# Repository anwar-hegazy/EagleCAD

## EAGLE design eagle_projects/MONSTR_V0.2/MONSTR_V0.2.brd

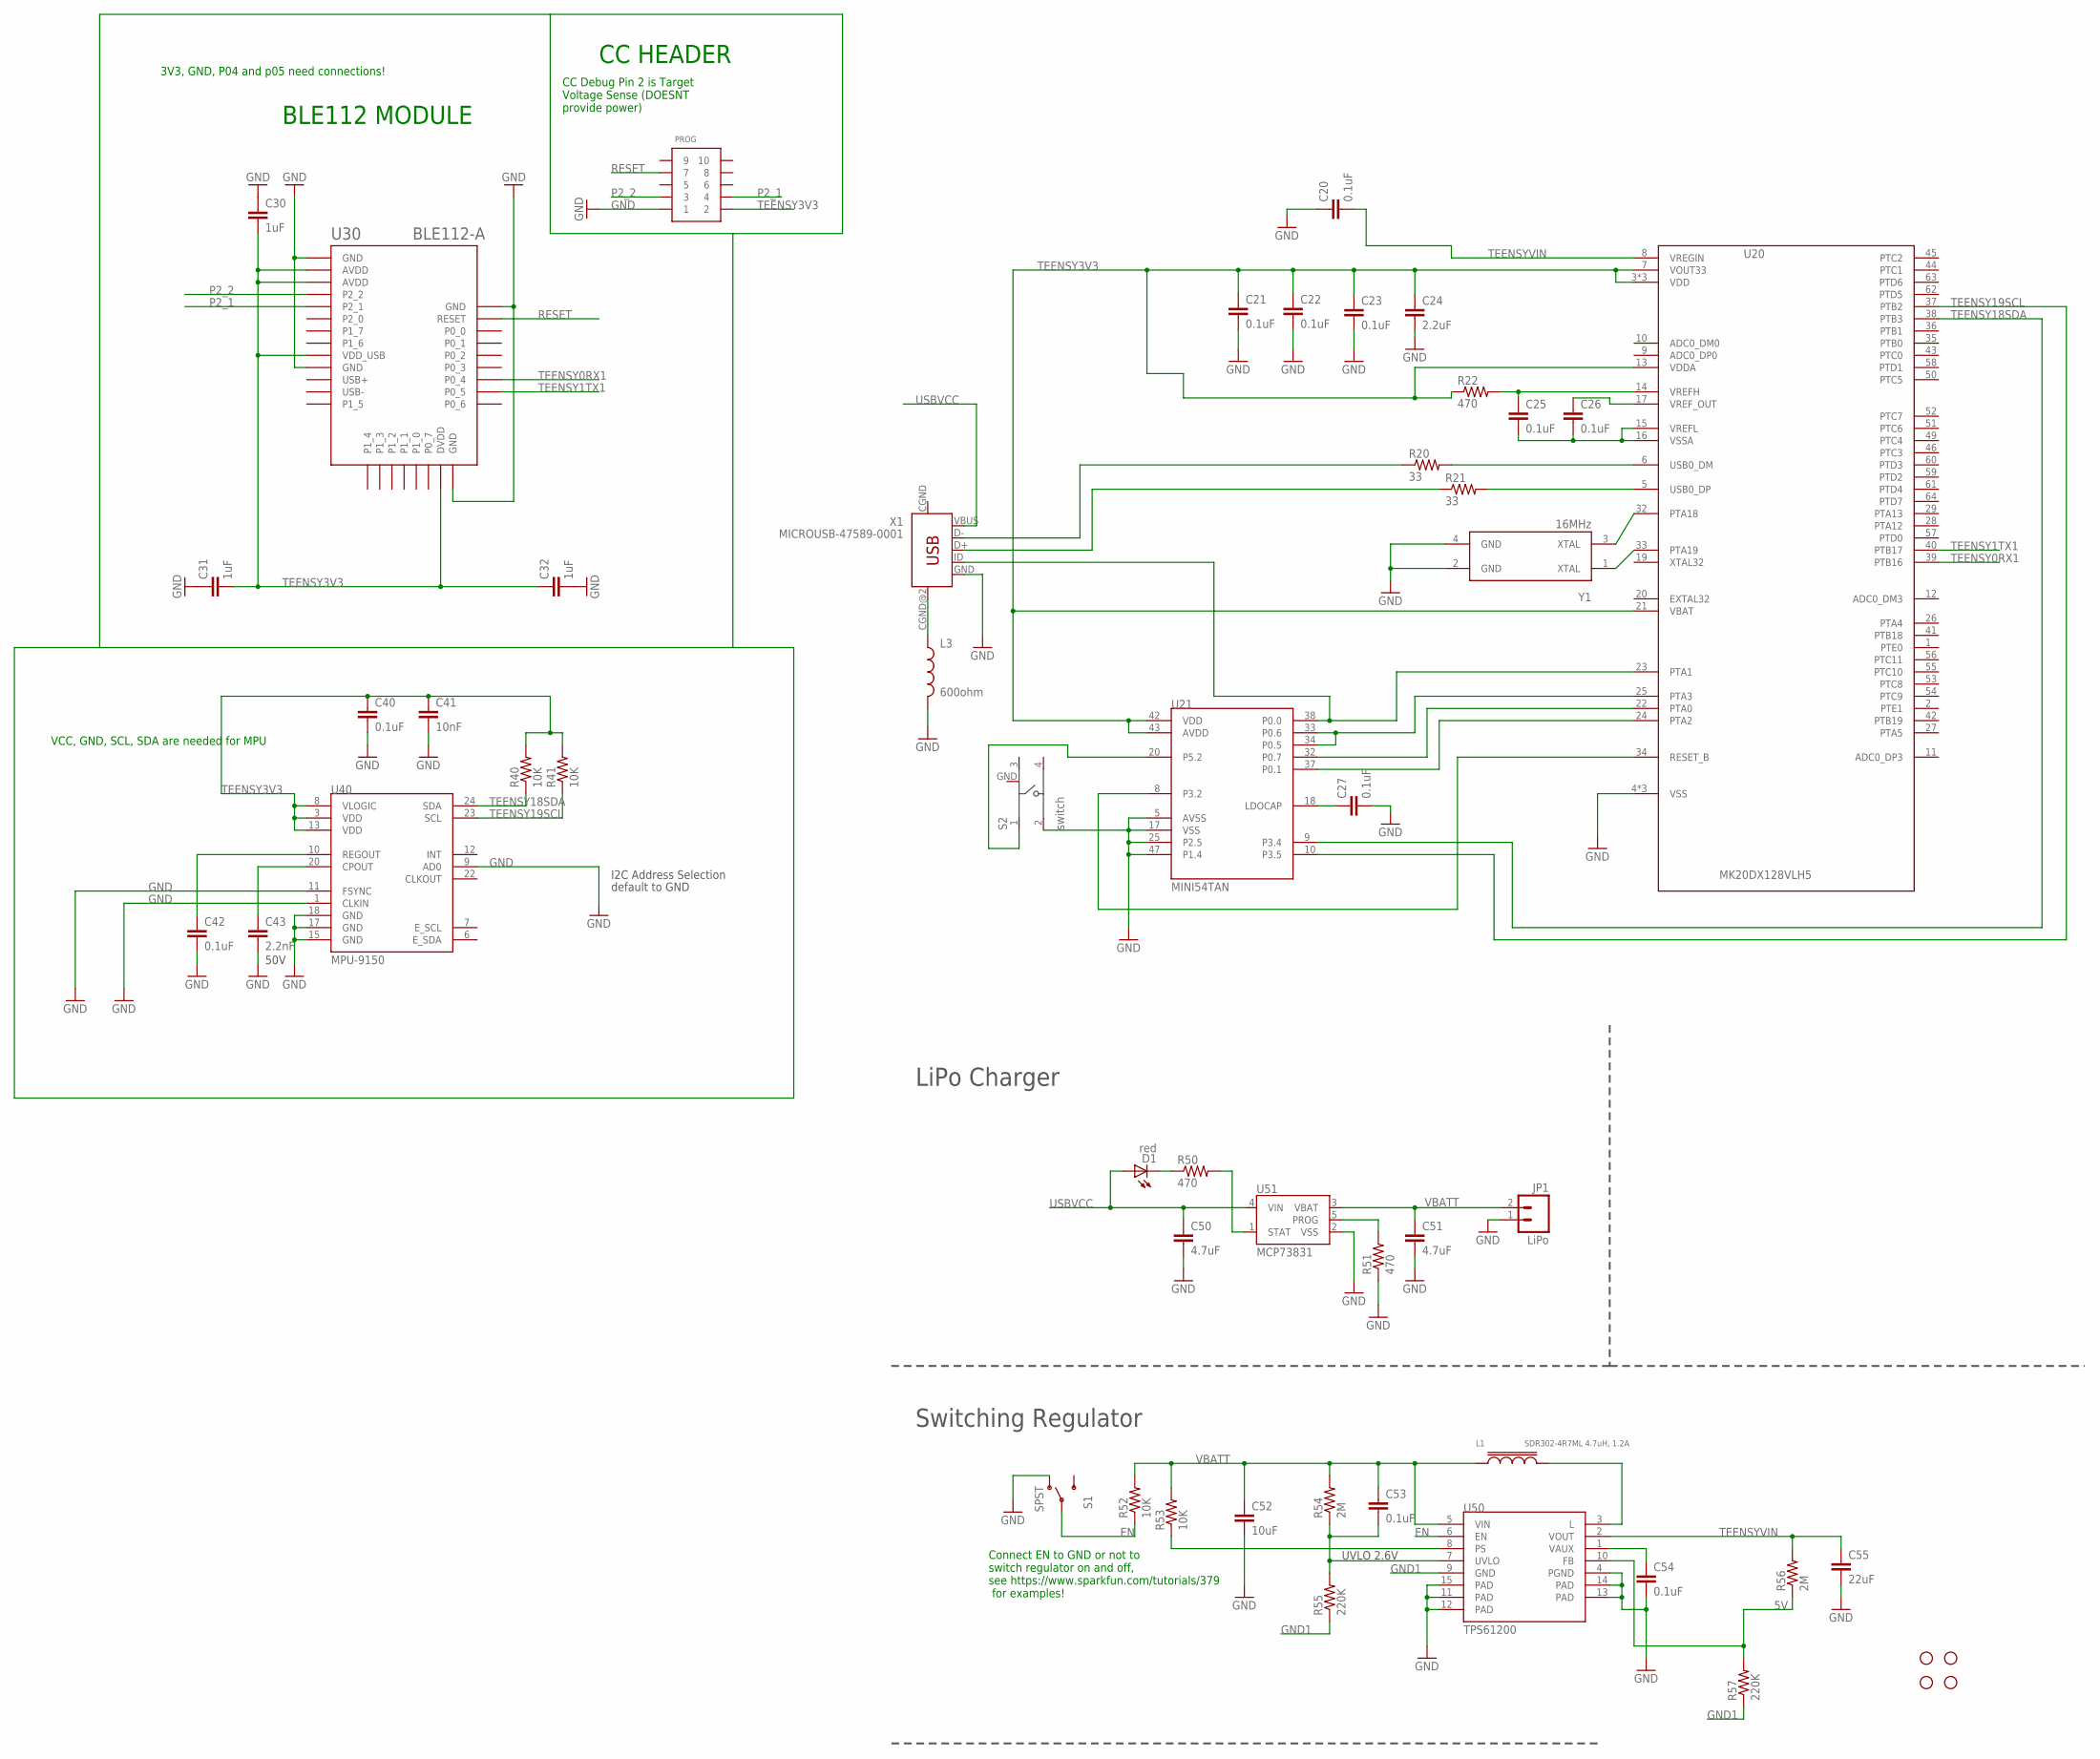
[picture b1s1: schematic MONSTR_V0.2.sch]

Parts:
C20, C21, C22, C23, C25, C26, C27, C40, C42, C53, C54: 0.1uF; 0402-CAP
C24: 2.2uF; 0402-CAP
C30, C31, C32: 1uF; 0402-CAP
C41: 10nF; 0402-CAP
C43: 2.2nF; 0402-CAP
C50, C51: 4.7uF; 0402-CAP
C52: 10uF; 0402-CAP
C55: 22uF; 0603-CAP
D1: red; LED-0603
JP1: LiPo; JST-2-SMD
JP7, JP8, JP9, JP10: STAND-OFF
L1: SDR302-4R7ML 4.7uH, 1.2A; BOURNS-SDR0302-SERIES-INDUCTOR
L3: 600ohm; 0805
PROG: CONN_5-2-FTSH-V; FTSH-105-DV
R20, R21: 33; 0402-RES
R22, R50, R51: 470; 0402-RES
R40, R41, R52, R53: 10K; 0402-RES
R54, R56: 2M; 0402-RES
R55, R57: 220K; 0402-RES
S1: SPST; SWITCH-SPST-SMD-A
S2: switch; 101-IG
U20: MK20DX128VLH5
U21: MINI54TAN
U30: BLE112-A
U40: MPU-9150; QFN-24-NP
U50: TPS61200; QFN-10_PAD
U51: MCP73831; SOT23-5
X1: MICROUSB-47589-0001
Y1: 16MHz; CRYSTAL-SMD-3.2_2.5MM

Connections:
5V: R56.1, R57.2, U50.10 (FB)
EN: R52.1, S1.2, U50.6 (EN)
GND: C20.1, C21.2, C22.2, C23.2, C24.2, C27.2, C30.1, C31.1, C32.2, C40.2, C41.2, C42.2, C43.2, C50.2, C51.2, C52.2, C54.2, C55.2, JP1.1, L3.2, PROG.1, R51.1, S1.1 (O), S2.2, S2.GND, U20.4 (VSS), U20.31 (VSS), U20.47 (VSS), U21.5 (AVSS), U21.17 (VSS), U21.25 (P2.5), U21.47 (P1.4), U30.GND1 (GND), U30.GND2 (GND), U30.GND3 (GND), U30.GND4 (GND), U40.1 (CLKIN), U40.9 (AD0), U40.11 (FSYNC), U40.15 (GND), U40.17 (GND), U40.18 (GND), U50.4 (PGND), U50.11 (PAD), U50.12 (PAD), U50.13 (PAD), U50.14 (PAD), U50.15 (PAD), U51.2 (VSS), X1.GND, Y1.2 (GND), Y1.4 (GND)
GND1: R55.1, R57.1, U50.9 (GND)
unnamed: C43.1, U40.20 (CPOUT)
unnamed: C42.1, U40.10 (REGOUT)
unnamed: R53.1, U50.8 (PS)
unnamed: R51.2, U51.5 (PROG)
unnamed: R50.2, U51.1 (STAT)
unnamed: U20.32 (PTA18), Y1.3 (XTAL)
unnamed: U20.33 (PTA19), Y1.1 (XTAL)
unnamed: C25.2, C26.2, U20.15 (VREFL), U20.16 (VSSA)
unnamed: R20.2, U20.6 (USB0_DM)
unnamed: R21.2, U20.5 (USB0_DP)
unnamed: R20.1, X1.D-
unnamed: R21.1, X1.D+
unnamed: L3.1, X1.CGND@2 (MTN4)
unnamed: C26.1, U20.17 (VREF_OUT)
unnamed: C25.1, R22.2, U20.14 (VREFH)
unnamed: U20.23 (PTA1), U21.38 (P0.0), X1.ID
unnamed: U20.25 (PTA3), U21.33 (P0.6), U21.34 (P0.5)
unnamed: U20.22 (PTA0), U21.32 (P0.7)
unnamed: U20.24 (PTA2), U21.37 (P0.1)
unnamed: S2.1, U21.20 (P5.2)
unnamed: U20.34 (RESET_B), U21.8 (P3.2)
unnamed: C27.1, U21.18 (LDOCAP)
unnamed: D1.C, R50.1
unnamed: L1.2, U50.3 (L)
unnamed: C54.1, U50.1 (VAUX)
P2_1: PROG.4, U30.P2_1
P2_2: PROG.3, U30.P2_2
RESET: PROG.7, U30.RESET
TEENSY0RX1: U20.39 (PTB16), U30.P0_4
TEENSY1TX1: U20.40 (PTB17), U30.P0_5
TEENSY3V3: C21.1, C22.1, C23.1, C24.1, C30.2, C31.2, C32.1, C40.1, C41.1, PROG.2, R22.1, R40.2, R41.2, U20.3 (VDD), U20.7 (VOUT33), U20.13 (VDDA), U20.21 (VBAT), U20.30 (VDD), U20.48 (VDD), U21.42 (VDD), U21.43 (AVDD), U30.AVDD1 (AVDD), U30.AVDD2 (AVDD), U30.DVDD, U30.VDD_USB, U40.3 (VDD), U40.8 (VLOGIC), U40.13 (VDD)
TEENSY18SDA: R40.1, U20.38 (PTB3), U21.9 (P3.4), U40.24 (SDA)
TEENSY19SCL: R41.1, U20.37 (PTB2), U21.10 (P3.5), U40.23 (SCL)
TEENSYVIN: C20.2, C55.1, R56.2, U20.8 (VREGIN), U50.2 (VOUT)
USBVCC: C50.1, D1.A, U51.4 (VIN), X1.VBUS
UVLO: C53.2, R54.1, R55.2, U50.7 (UVLO)
VBATT: C51.1, C52.1, C53.1, JP1.2, L1.1, R52.2, R53.2, R54.2, U50.5 (VIN), U51.3 (VBAT)

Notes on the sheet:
50V
I2C Address Selection
default to GND
CC HEADER
BLE112 MODULE
VCC, GND, SCL, SDA are needed for MPU
UVLO 2.6V
LiPo Charger
Switching Regulator
Connect EN to GND or not to switch regulator on and off, see https://www.sparkfun.com/tutorials/379 for examples!
3V3, GND, P04 and p05 need connections!
CC Debug Pin 2 is Target Voltage Sense (DOESNT provide power)

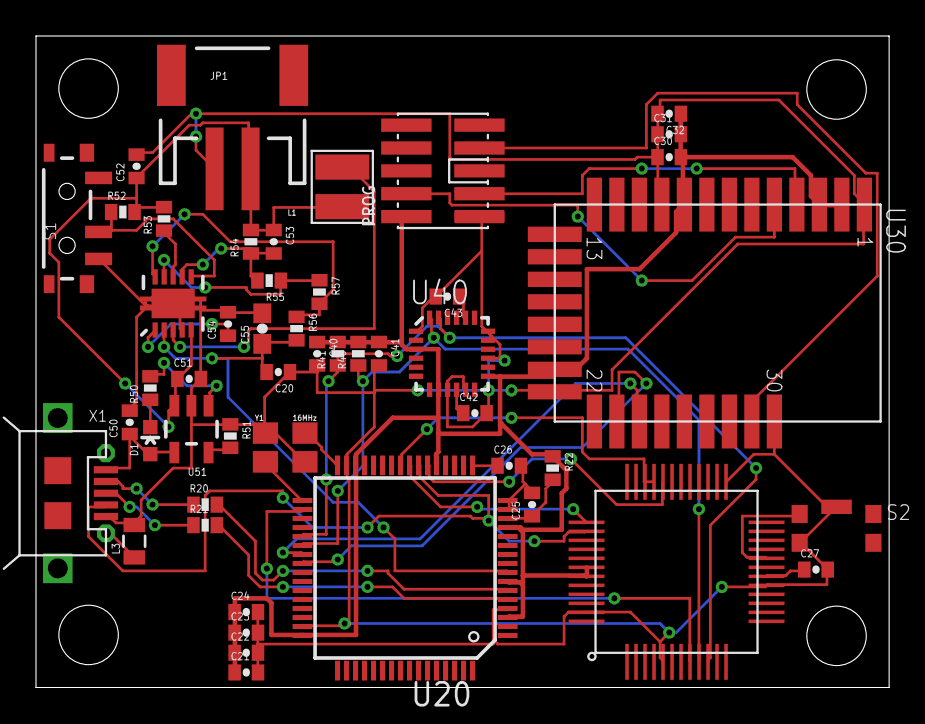
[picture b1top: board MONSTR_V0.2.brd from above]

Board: 2 copper layers, 47.4 x 36.2 mm, 53 parts (0 on the bottom side), 41 nets.

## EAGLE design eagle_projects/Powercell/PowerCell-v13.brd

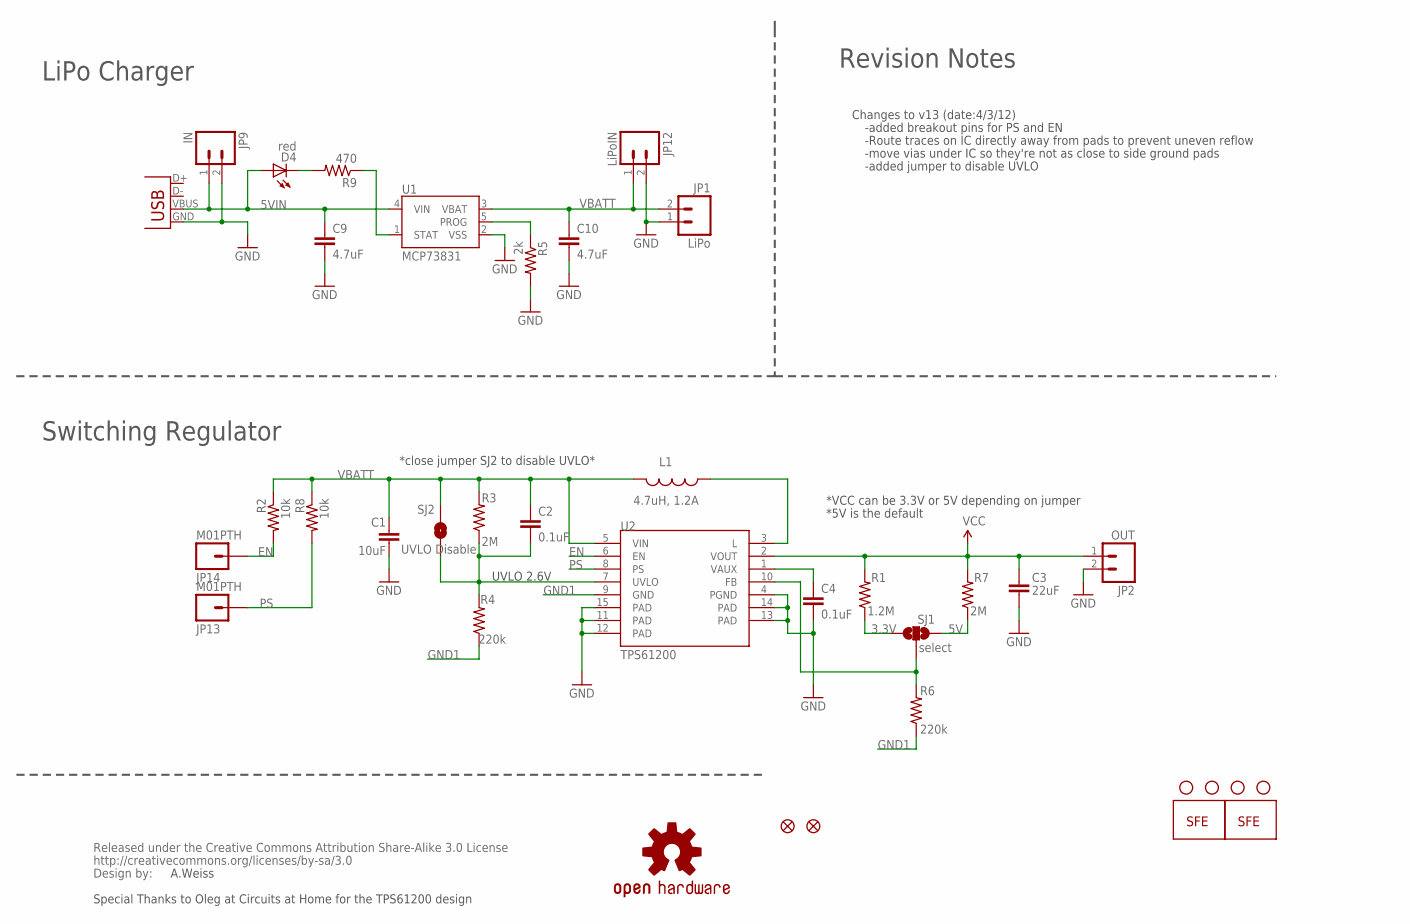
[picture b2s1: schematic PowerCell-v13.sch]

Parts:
C1: 10uF; 1206
C2, C4: 0.1uF; 0402-CAP
C3: 22uF; 0805
C9, C10: 4.7uF; 0402-CAP
D4: red; LED-0603
JP1: LiPo; JST-2-SMD
JP2: OUT; 1X02
JP3: LOGO-SFENEW; SFE-NEW-WEBLOGO
JP4: LOGO-SFESK; SFE-LOGO-FLAME
JP5, JP6, JP7, JP8: STAND-OFF
JP9: IN; 1X02
JP12: LiPoIN; 1X02
JP13, JP14: M01PTH; 1X01
JP15, JP16: FIDUCIALUFIDUCIAL; MICRO-FIDUCIAL
L1: 4.7uH, 1.2A; CDRH2D09
R1: 1.2M; 0402-RES
R2, R8: 10k; 0402-RES
R3, R7: 2M; 0402-RES
R4, R6: 220k; 0402-RES
R5: 2k; 0402-RES
R9: 470; 0402-RES
SJ1: select; SJ_3_PASTE2&3
SJ2: UVLO Disable; SJ_2S-NO
U1: MCP73831; SOT23-5
U2: TPS61200; QFN-10_PAD
U$1: OSHW-LOGOS; OSHW-LOGO-S
U$2: CREATIVE_COMMONS
X1: USB-MICROB

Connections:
3.3V: R1.1, SJ1.1
5V: R7.1, SJ1.3
5VIN: C9.1, D4.A, JP9.1, U1.4 (VIN), X1.VBUS
EN: JP14.1, R2.2, U2.6 (EN)
FB: R6.2, SJ1.2, U2.10 (FB)
GND: C1.2, C3.2, C4.2, C9.2, C10.2, JP1.1, JP2.2, JP9.2, JP12.2, R5.2, U1.2 (VSS), U2.4 (PGND), U2.11 (PAD), U2.12 (PAD), U2.13 (PAD), U2.14 (PAD), U2.15 (PAD), X1.GND
GND1: R4.1, R6.1, U2.9 (GND)
unnamed: C4.1, U2.1 (VAUX)
unnamed: L1.P$1 (1), U2.3 (L)
unnamed: D4.C, R9.2
unnamed: R5.1, U1.5 (PROG)
unnamed: R9.1, U1.1 (STAT)
PS: JP13.1, R8.2, U2.8 (PS)
UVLO: C2.2, R3.1, R4.2, SJ2.1, U2.7 (UVLO)
VBATT: C1.1, C2.1, C10.1, JP1.2, JP12.1, L1.P$2 (2), R2.1, R3.2, R8.1, SJ2.2, U1.3 (VBAT), U2.5 (VIN)
VCC: C3.1, JP2.1, R1.2, R7.2, U2.2 (VOUT)

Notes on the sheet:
UVLO 2.6V
Changes to v13 (date:4/3/12)
-added breakout pins for PS and EN
-Route traces on IC directly away from pads to prevent uneven reflow
-move vias under IC so they're not as close to side ground pads
*close jumper SJ2 to disable UVLO*
-added jumper to disable UVLO
A.Weiss
Special Thanks to Oleg at Circuits at Home for the TPS61200 design
LiPo Charger
Switching Regulator
Revision Notes
*VCC can be 3.3V or 5V depending on jumper
*5V is the default

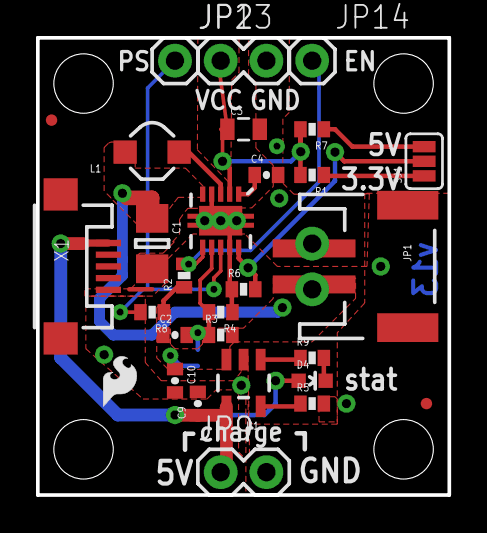
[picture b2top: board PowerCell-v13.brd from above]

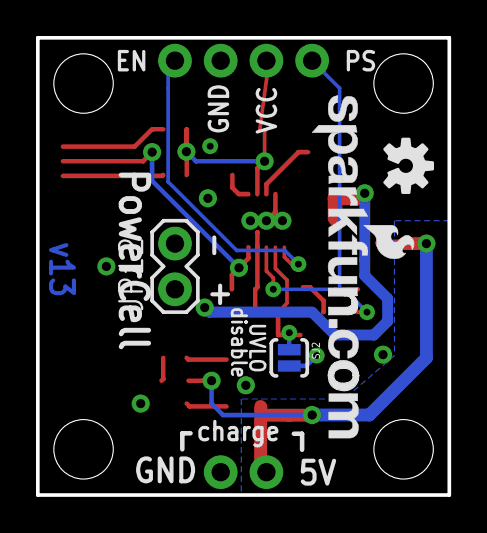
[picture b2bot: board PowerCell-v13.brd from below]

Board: 2 copper layers, 22.9 x 25.4 mm, 38 parts (4 on the bottom side), 16 nets.

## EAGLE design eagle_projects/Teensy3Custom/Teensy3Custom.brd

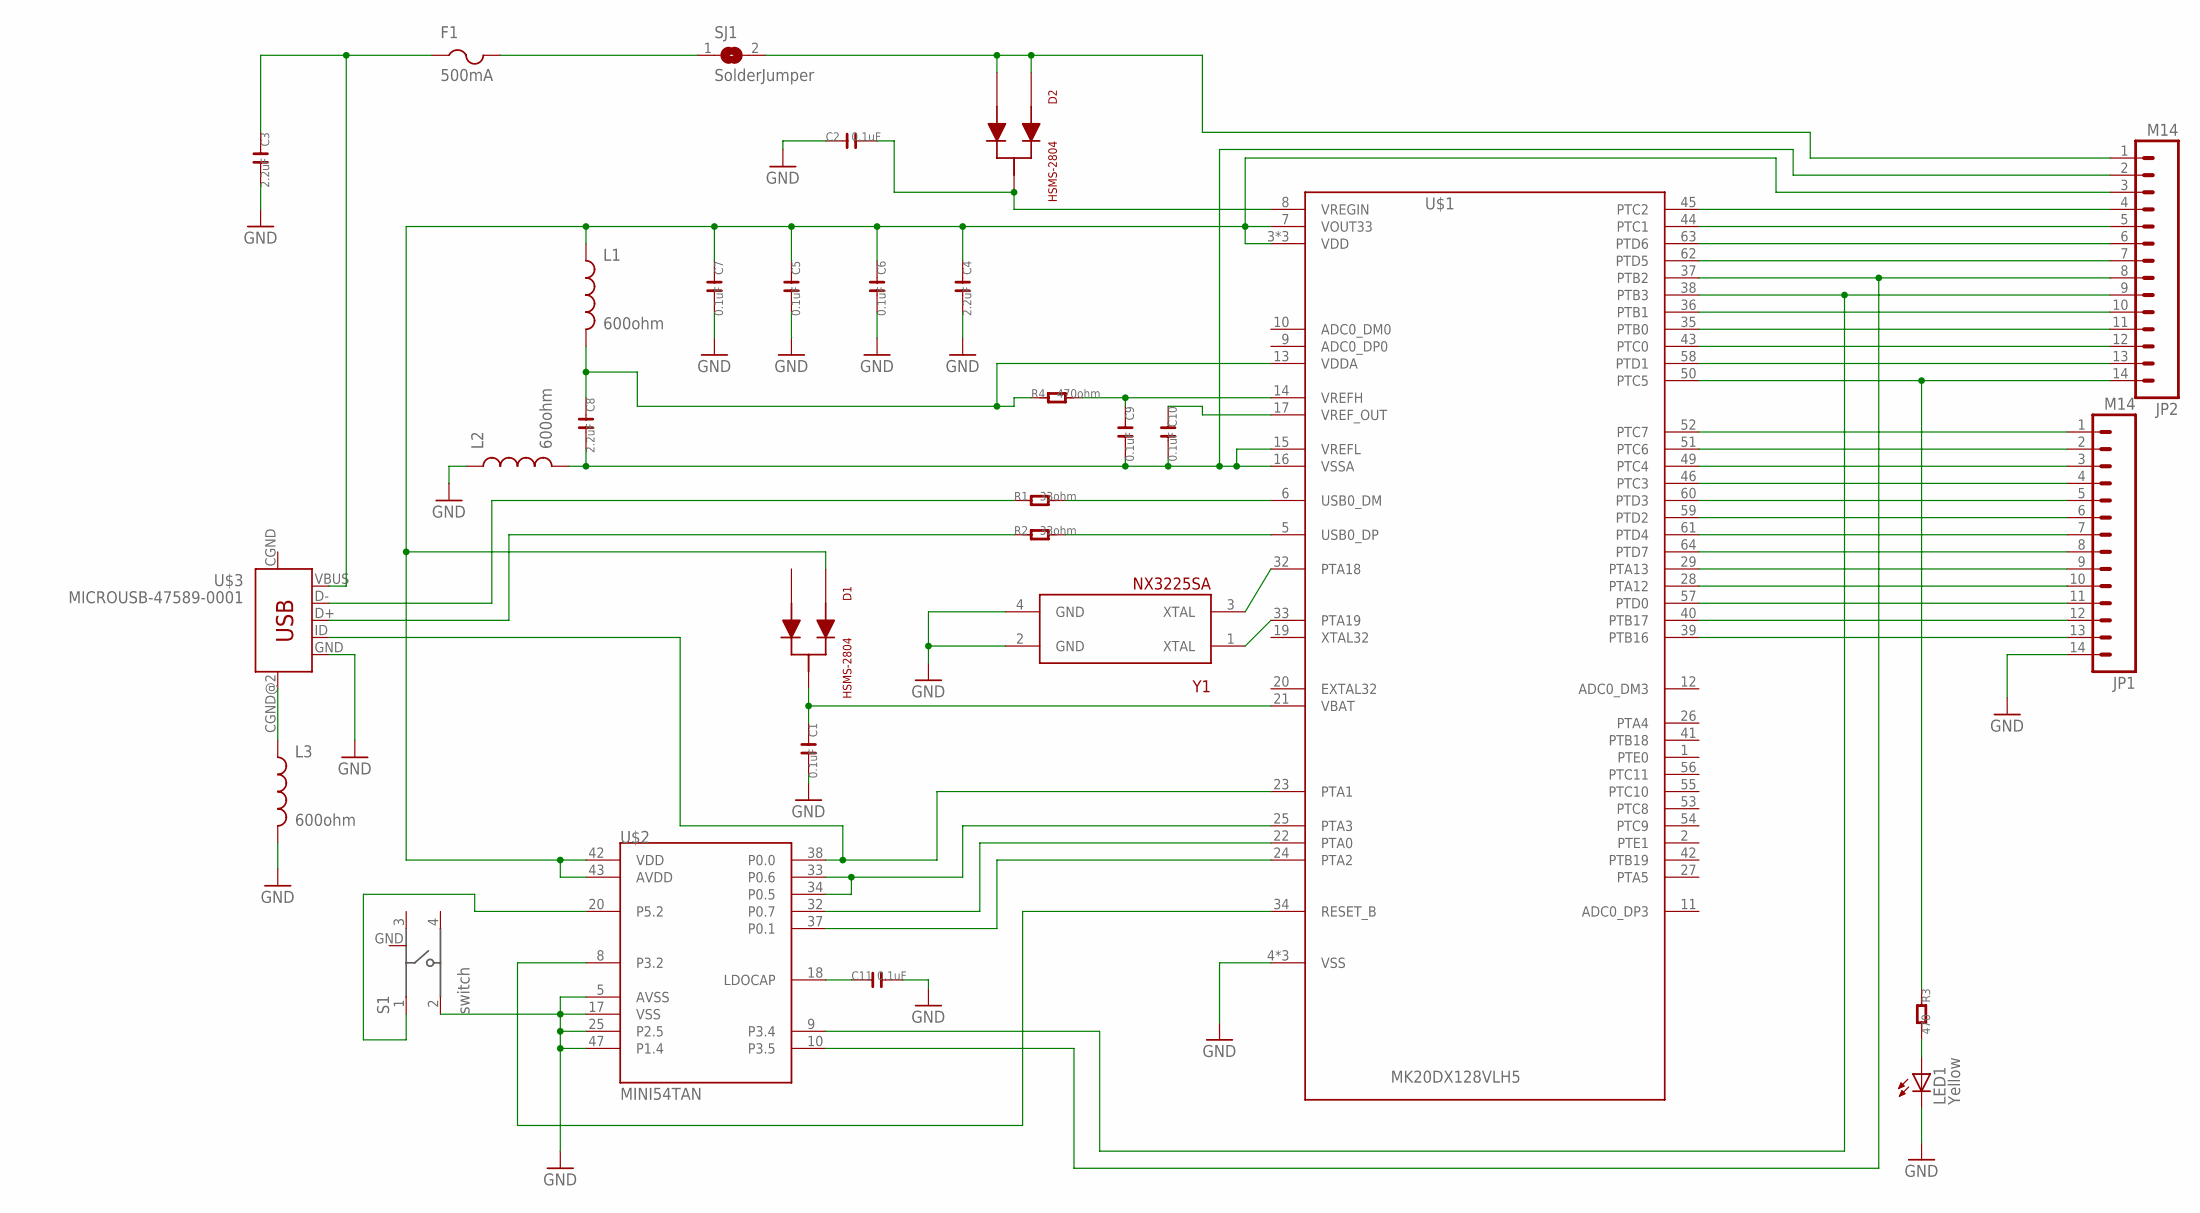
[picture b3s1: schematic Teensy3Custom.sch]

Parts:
C1, C2, C5, C6, C7, C9, C10, C11: 0.1uF; C0603
C3, C4, C8: 2.2uF; C0603
D1, D2: HSMS-2804; SOT-23-DIODE
F1: 500mA; R1206
JP1, JP2: M14; 1X14
L1, L2, L3: 600ohm; 0805
LED1: Yellow; CHIP-LED0603
R1, R2: 33ohm; R0603
R3: 470; R0603
R4: 470ohm; R0603
S1: switch; 101-IG
SJ1: SolderJumper; SJ
U$1: MK20DX128VLH5
U$2: MINI54TAN
U$3: MICROUSB-47589-0001
Y1: NX3225SA; CRYSTAL-SMD-3.2_2.5MM

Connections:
GND: C1.2, C2.1, C3.2, C4.2, C5.2, C6.2, C7.2, C11.2, JP1.14, L2.1, L3.2, LED1.C, S1.2, S1.GND, U$1.4 (VSS), U$1.31 (VSS), U$1.47 (VSS), U$2.5 (AVSS), U$2.17 (VSS), U$2.25 (P2.5), U$2.47 (P1.4), U$3.GND, Y1.2 (GND), Y1.4 (GND)
unnamed: U$1.32 (PTA18), Y1.3 (XTAL)
unnamed: U$1.33 (PTA19), Y1.1 (XTAL)
unnamed: C1.1, D1.3 (OUT), U$1.21 (VBAT)
unnamed: D2.1 (IN), D2.2 (IN), JP2.1, SJ1.2
unnamed: F1.2, SJ1.1
unnamed: C3.1, F1.1, U$3.VBUS
unnamed: C2.2, D2.3 (OUT), U$1.8 (VREGIN)
unnamed: C4.1, C5.1, C6.1, C7.1, D1.1 (IN), JP2.3, L1.1, U$1.3 (VDD), U$1.7 (VOUT33), U$1.30 (VDD), U$1.48 (VDD), U$2.42 (VDD), U$2.43 (AVDD)
unnamed: C8.2, C9.2, C10.2, JP2.2, L2.2, U$1.15 (VREFL), U$1.16 (VSSA)
unnamed: C8.1, L1.2, R4.1, U$1.13 (VDDA)
unnamed: R2.2, U$1.5 (USB0_DP)
unnamed: R1.1, U$3.D-
unnamed: R1.2, U$1.6 (USB0_DM)
unnamed: R2.1, U$3.D+
unnamed: L3.1, U$3.CGND@2 (MTN4)
unnamed: U$1.25 (PTA3), U$2.33 (P0.6), U$2.34 (P0.5)
unnamed: C10.1, U$1.17 (VREF_OUT)
unnamed: C9.1, R4.2, U$1.14 (VREFH)
unnamed: LED1.A, R3.2
unnamed: JP2.14, R3.1, U$1.50 (PTC5)
unnamed: S1.1, U$2.20 (P5.2)
unnamed: U$1.23 (PTA1), U$2.38 (P0.0), U$3.ID
unnamed: U$1.22 (PTA0), U$2.32 (P0.7)
unnamed: U$1.24 (PTA2), U$2.37 (P0.1)
unnamed: JP2.9, U$1.38 (PTB3), U$2.9 (P3.4)
unnamed: JP2.8, U$1.37 (PTB2), U$2.10 (P3.5)
unnamed: U$1.34 (RESET_B), U$2.8 (P3.2)
unnamed: JP2.4, U$1.45 (PTC2)
unnamed: JP2.5, U$1.44 (PTC1)
unnamed: JP2.6, U$1.63 (PTD6)
unnamed: JP2.7, U$1.62 (PTD5)
unnamed: JP2.10, U$1.36 (PTB1)
unnamed: JP2.11, U$1.35 (PTB0)
unnamed: JP2.12, U$1.43 (PTC0)
unnamed: JP2.13, U$1.58 (PTD1)
unnamed: JP1.1, U$1.52 (PTC7)
unnamed: JP1.13, U$1.39 (PTB16)
unnamed: JP1.12, U$1.40 (PTB17)
unnamed: JP1.11, U$1.57 (PTD0)
unnamed: JP1.10, U$1.28 (PTA12)
unnamed: JP1.9, U$1.29 (PTA13)
unnamed: JP1.8, U$1.64 (PTD7)
unnamed: JP1.7, U$1.61 (PTD4)
unnamed: JP1.6, U$1.59 (PTD2)
unnamed: JP1.5, U$1.60 (PTD3)
unnamed: JP1.4, U$1.46 (PTC3)
unnamed: JP1.3, U$1.49 (PTC4)
unnamed: JP1.2, U$1.51 (PTC6)
unnamed: C11.1, U$2.18 (LDOCAP)

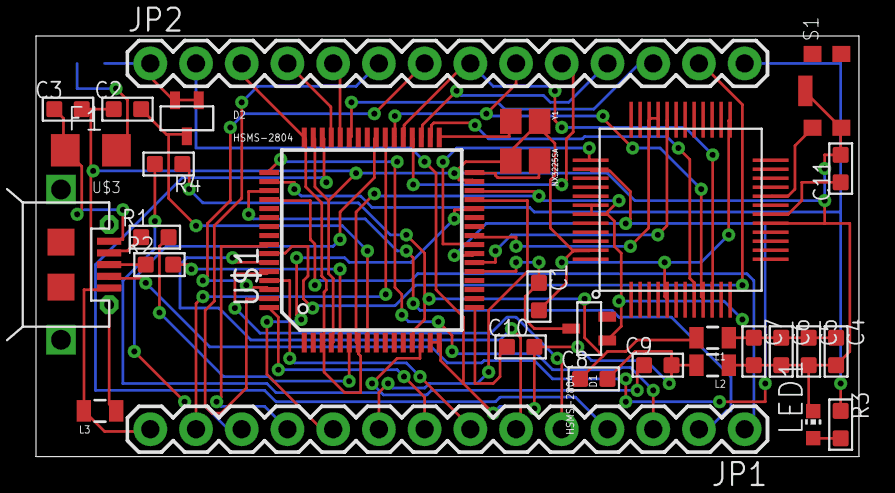
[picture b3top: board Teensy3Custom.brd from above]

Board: 2 copper layers, 45.7 x 23.4 mm, 30 parts (1 on the bottom side), 50 nets.

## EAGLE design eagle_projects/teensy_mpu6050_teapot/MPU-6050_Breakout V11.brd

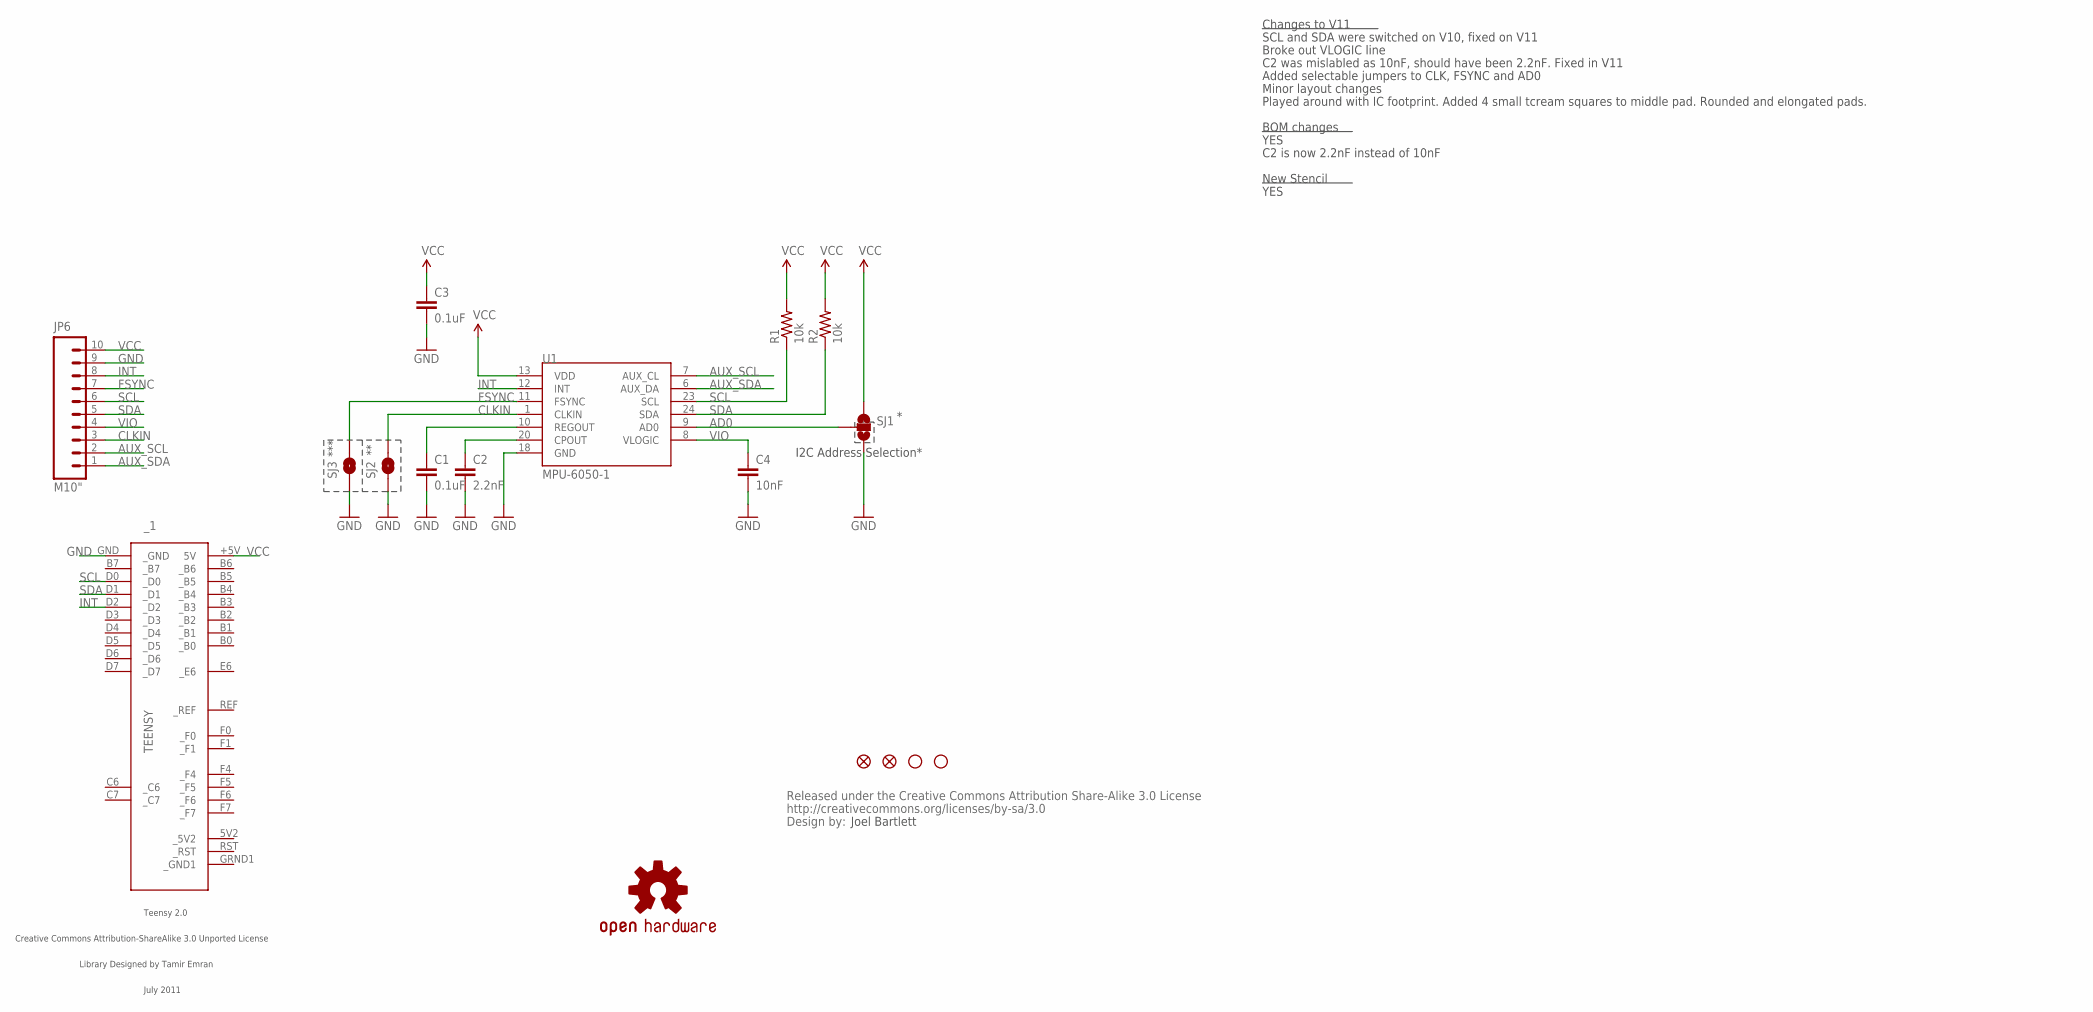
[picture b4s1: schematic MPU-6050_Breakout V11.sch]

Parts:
C1, C3: 0.1uF; 0402-CAP
C2: 2.2nF; 0402-CAP
C4: 10nF; 0402-CAP
JP2, JP5: FIDUCIALUFIDUCIAL; MICRO-FIDUCIAL
JP3, JP4: STAND-OFFTIGHT; STAND-OFF-TIGHT
JP6: M10"; 1X10
R1, R2: 10k; 0402-RES
SJ1: SOLDERJUMPER_2WAYPASTE2&3; SJ_3_PASTE2&3
SJ2, SJ3: SOLDERJUMPERTRACE; SJ_2S-TRACE
U1: MPU-6050-1; QFN-24-4MM2
U3: CREATIVE_COMMONS
U$1: OSHW-LOGOS; OSHW-LOGO-S
_1: TEENSY

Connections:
AD0: SJ1.2, U1.9 (AD0)
AUX_SCL: JP6.2, U1.7 (AUX_CL)
AUX_SDA: JP6.1, U1.6 (AUX_DA)
CLKIN: JP6.3, SJ2.2, U1.1 (CLKIN)
FSYNC: JP6.7, SJ3.2, U1.11 (FSYNC)
GND: C1.2, C2.2, C3.2, C4.2, JP6.9, SJ1.3, SJ2.1, SJ3.1, U1.18 (GND), _1.GND (_GND)
INT: JP6.8, U1.12 (INT), _1.D2 (_D2)
unnamed: C2.1, U1.20 (CPOUT)
unnamed: C1.1, U1.10 (REGOUT)
SCL: JP6.6, R1.1, U1.23 (SCL), _1.D0 (_D0)
SDA: JP6.5, R2.1, U1.24 (SDA), _1.D1 (_D1)
VCC: C3.1, JP6.10, R1.2, R2.2, SJ1.1, U1.13 (VDD), _1.+5V (5V)
VIO: C4.1, JP6.4, U1.8 (VLOGIC)

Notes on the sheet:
Joel Bartlett
I2C Address Selection*
***
Changes to V11
SCL and SDA were switched on V10, fixed on V11
C2 was mislabled as 10nF, should have been 2.2nF. Fixed in V11
Broke out VLOGIC line
BOM changes
New Stencil
YES
C2 is now 2.2nF instead of 10nF
Minor layout changes
Added selectable jumpers to CLK, FSYNC and AD0
Played around with IC footprint. Added 4 small tcream squares to middle pad. Rounded and elongated pads.

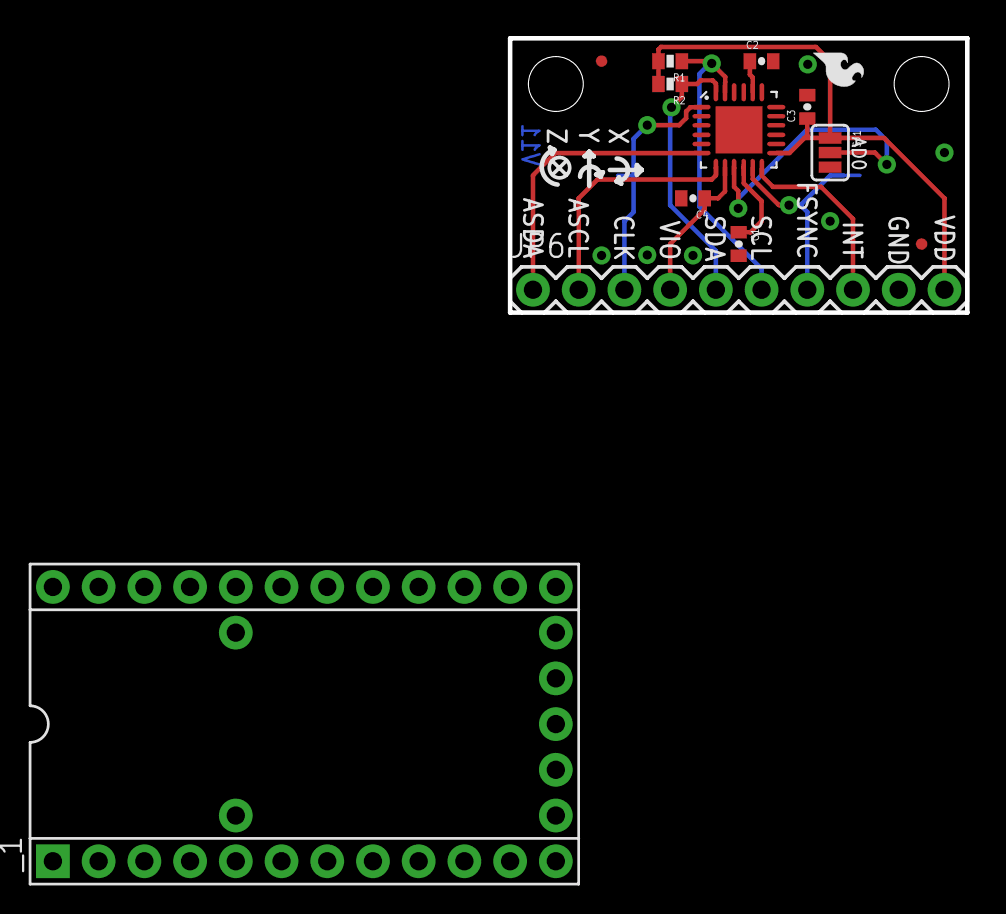
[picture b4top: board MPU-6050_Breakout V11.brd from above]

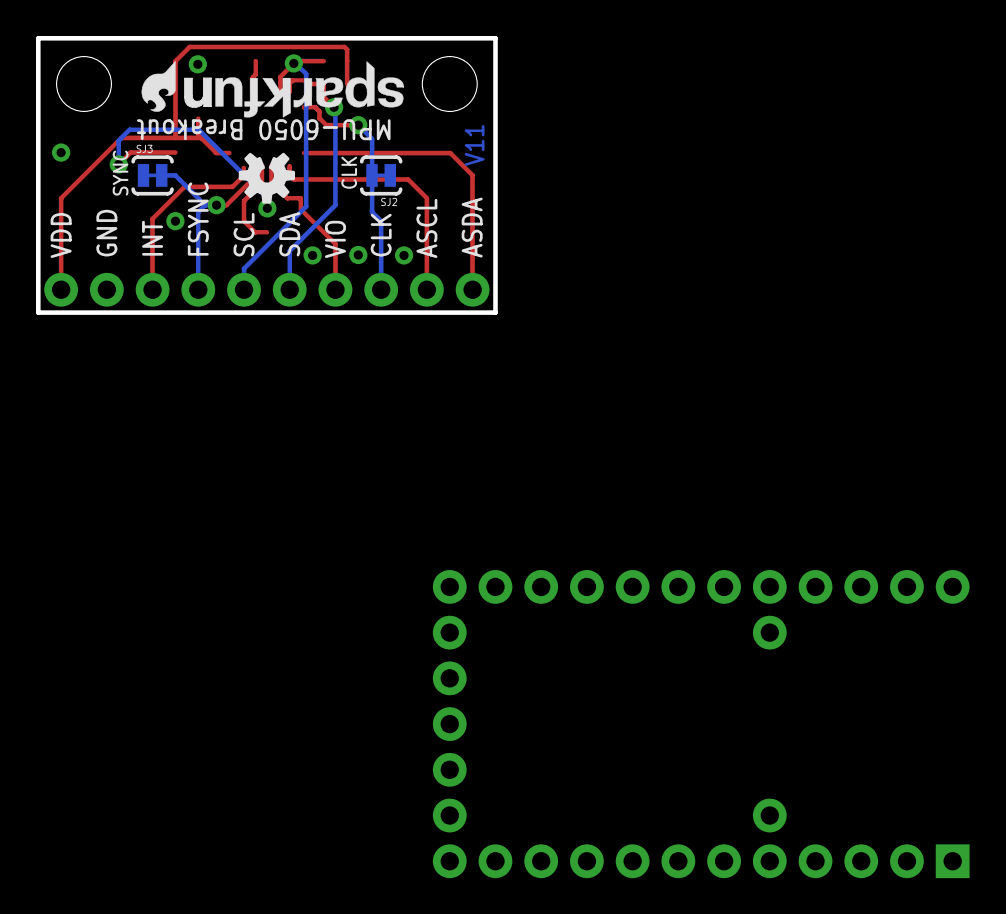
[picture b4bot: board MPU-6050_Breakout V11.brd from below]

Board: 2 copper layers, 25.4 x 15.2 mm, 21 parts (5 on the bottom side), 13 nets.

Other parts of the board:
U$2, U$3: SFE-LOGO-FLAME
U$4: SFE-NEW-WEB

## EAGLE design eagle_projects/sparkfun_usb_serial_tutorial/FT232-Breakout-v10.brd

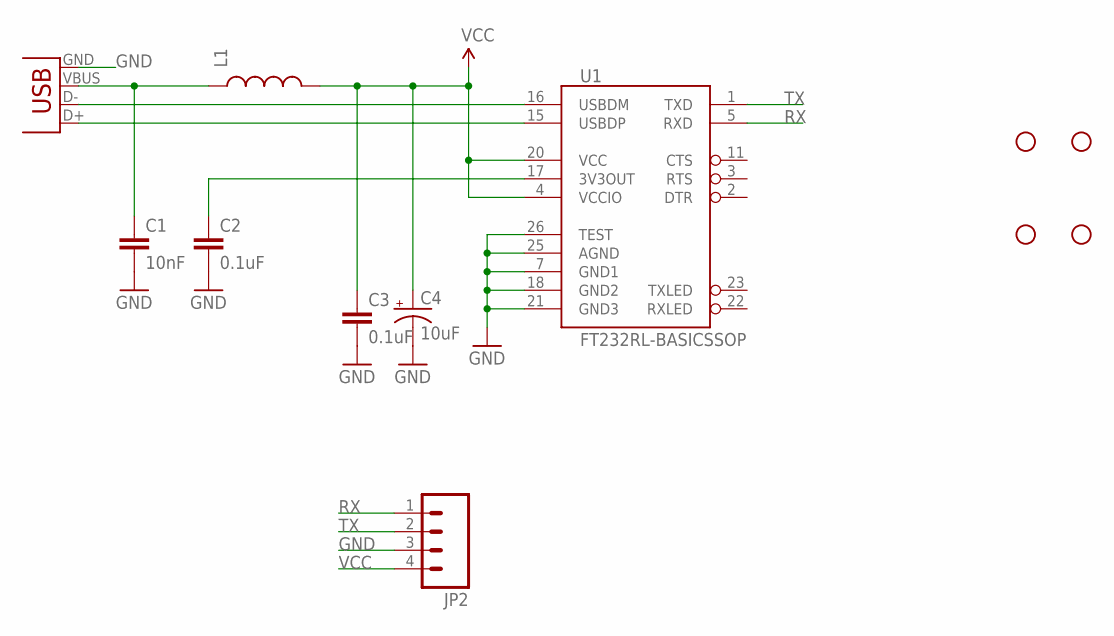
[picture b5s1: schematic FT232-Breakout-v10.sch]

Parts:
C1: 10nF; 0603-CAP
C2, C3: 0.1uF; 0603-CAP
C4: 10uF; EIA3216
JP1: USB-B; USB-B-PTH
JP2: M04PTH; 1X04
L1: INDUCTOR0603; 0603
STANDOFF1, STANDOFF2, STANDOFF3, STANDOFF4: STAND-OFF
U1: FT232RL-BASICSSOP; SSOP28DB

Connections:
GND: C1.2, C2.2, C3.2, C4.C (-), JP1.GND, JP2.3, U1.7 (GND1), U1.18 (GND2), U1.21 (GND3), U1.25 (AGND), U1.26 (TEST)
unnamed: C1.1, JP1.VBUS, L1.1
unnamed: C2.1, U1.17 (3V3OUT)
unnamed: JP1.D-, U1.16 (USBDM)
unnamed: JP1.D+, U1.15 (USBDP)
RX: JP2.1, U1.5 (RXD)
TX: JP2.2, U1.1 (TXD)
VCC: C3.1, C4.A (+), JP2.4, L1.2, U1.4 (VCCIO), U1.20 (VCC)

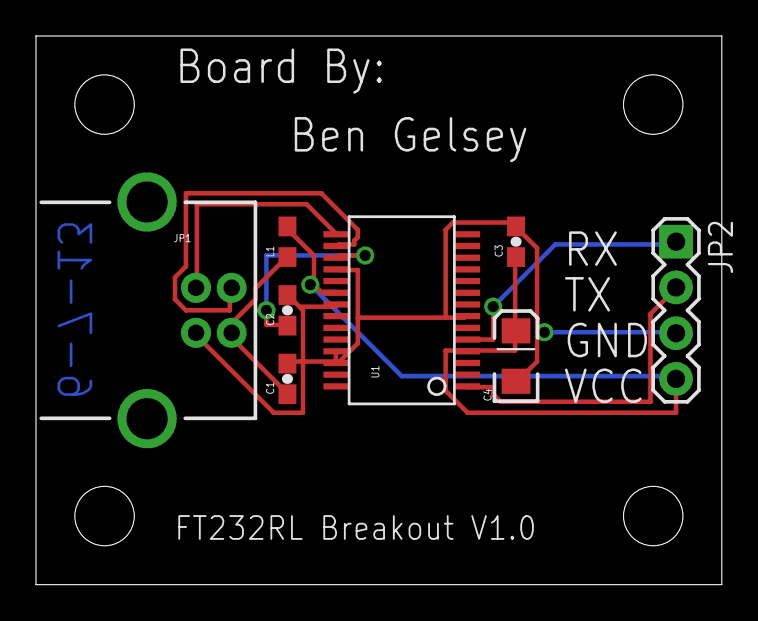
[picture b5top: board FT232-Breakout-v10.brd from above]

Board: 2 copper layers, 38.1 x 30.5 mm, 12 parts (0 on the bottom side), 8 nets.

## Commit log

2013-10-17 v1.00 of Teensy breakout board complete/routed
2013-10-23 MONSTR_V0.1 PCB is ready!
2013-10-23 MONSTR_V0.2 PCB at 1.866x1.425 inches

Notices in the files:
parts and their libraries:
SparkFun-Sensors: Licensing: CC v3.0 Share-Alike You are welcome to use this library for commercial purposes.
SparkFun-Aesthetics: Released under the Creative Commons Attribution Share-Alike 3.0 License
SparkFun-Aesthetics: http://creativecommons.org/licenses/by-sa/3.0
